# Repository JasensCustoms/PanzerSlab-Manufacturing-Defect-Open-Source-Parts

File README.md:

# Panzer SLAB — Manufacturing Defect Compatible Parts

Compatible replacement parts for the Panzer SLAB manufacturing defect. This repository holds basic PCB outlines, cable pinouts, and related files. You are welcome to fix errors, add context, and contribute to the repo.

## What's in This Repo

- `Main PCB/` — main PCB design files
- `Plexi Overlay/` — plexi overlay cut file / art template (all SLABs)
- `AUX PCB Files/` — AUX PCB design and production files
- `USB C PCB Files/` — USB-C PCB design and production files
- `3D Printed Parts/` — 3D-printable parts (main PCB fix spacers and taller aux button)

## Community & Discussion

Questions, ideas, or just want to talk builds? Join the Jasen's Customs Discord: [discord.gg/UJmNMunTqa](https://discord.gg/UJmNMunTqa)

## License — Personal, Non-Commercial Use Only

Copyright © 2026 Jasen Hicks ([www.JasensCustoms.com](https://www.JasensCustoms.com)). All rights reserved.

These designs are provided **solely for personal, private, non-commercial use.** You may build units for yourself, modify the designs for your own projects, and share the unmodified files (with attribution and the license intact). You may **not** sell parts, kits, units, or derivatives, manufacture for profit, or use these files commercially in any way.

Full terms — including the **No Warranty** and **No Support** notices — are in [LICENSE.md](LICENSE.md). By downloading, copying, or using any file in this repository, you agree to them.

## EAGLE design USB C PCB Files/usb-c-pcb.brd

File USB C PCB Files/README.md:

# USB C PCB Files

Design and production files for the SLAB USB-C PCB.

## What's in This Folder

- `usb-c-pcb.brd` / `usb-c-pcb.sch` — Autodesk EagleCAD board and schematic files
- `usb-c-pcb_2025-09-19.zip` — production files

## License & Community

Part of the [Panzer SLAB — Manufacturing Defect Compatible Parts](../README.md) repository. Provided for **personal, non-commercial use only** — full terms in [LICENSE.md](../LICENSE.md). Questions? Join the Jasen's Customs Discord: [discord.gg/UJmNMunTqa](https://discord.gg/UJmNMunTqa)

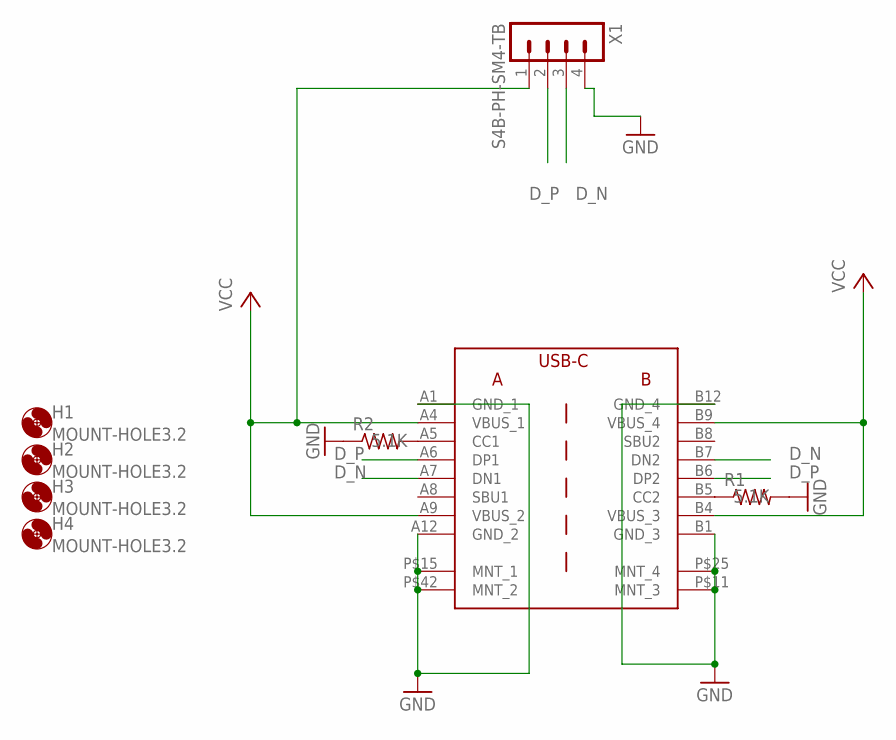
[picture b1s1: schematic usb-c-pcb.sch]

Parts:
H1, H2, H3, H4: MOUNT-HOLE3.2; 3,2
R1, R2: 5.1K; R0402
U$1: USB_TAYPE_C_16P
X1: S4B-PH-SM4-TB

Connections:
D_N: U$1.A7 (DN1), U$1.B7 (DN2), X1.3
D_P: U$1.A6 (DP1), U$1.B6 (DP2), X1.2
GND: R1.2, R2.1, U$1.A1 (GND_1), U$1.A12 (GND_2), U$1.B1 (GND_3), U$1.B12 (GND_4), U$1.P$11 (MNT_3), U$1.P$15 (MNT_1), U$1.P$25 (MNT_4), U$1.P$42 (MNT_2), X1.4
unnamed: R1.1, U$1.B5 (CC2)
unnamed: R2.2, U$1.A5 (CC1)
VCC: U$1.A4 (VBUS_1), U$1.A9 (VBUS_2), U$1.B4 (VBUS_3), U$1.B9 (VBUS_4), X1.1

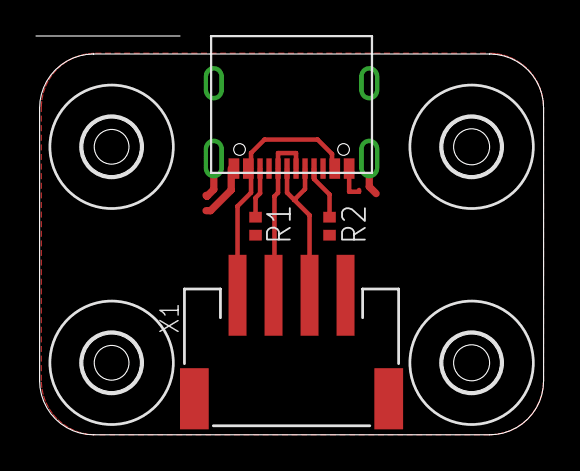
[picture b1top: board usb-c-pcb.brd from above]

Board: 2 copper layers, 28.2 x 22.2 mm, 8 parts (0 on the bottom side), 6 nets.

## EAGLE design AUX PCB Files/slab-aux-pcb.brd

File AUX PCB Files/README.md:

# AUX PCB Files

Design and production files for the SLAB AUX PCB.

## What's in This Folder

- `slab-aux-pcb.brd` / `slab-aux-pcb.sch` — Autodesk EagleCAD board and schematic files
- `slab-aux-pcb_2025-09-11.zip` — production files

## License & Community

Part of the [Panzer SLAB — Manufacturing Defect Compatible Parts](../README.md) repository. Provided for **personal, non-commercial use only** — full terms in [LICENSE.md](../LICENSE.md). Questions? Join the Jasen's Customs Discord: [discord.gg/UJmNMunTqa](https://discord.gg/UJmNMunTqa)

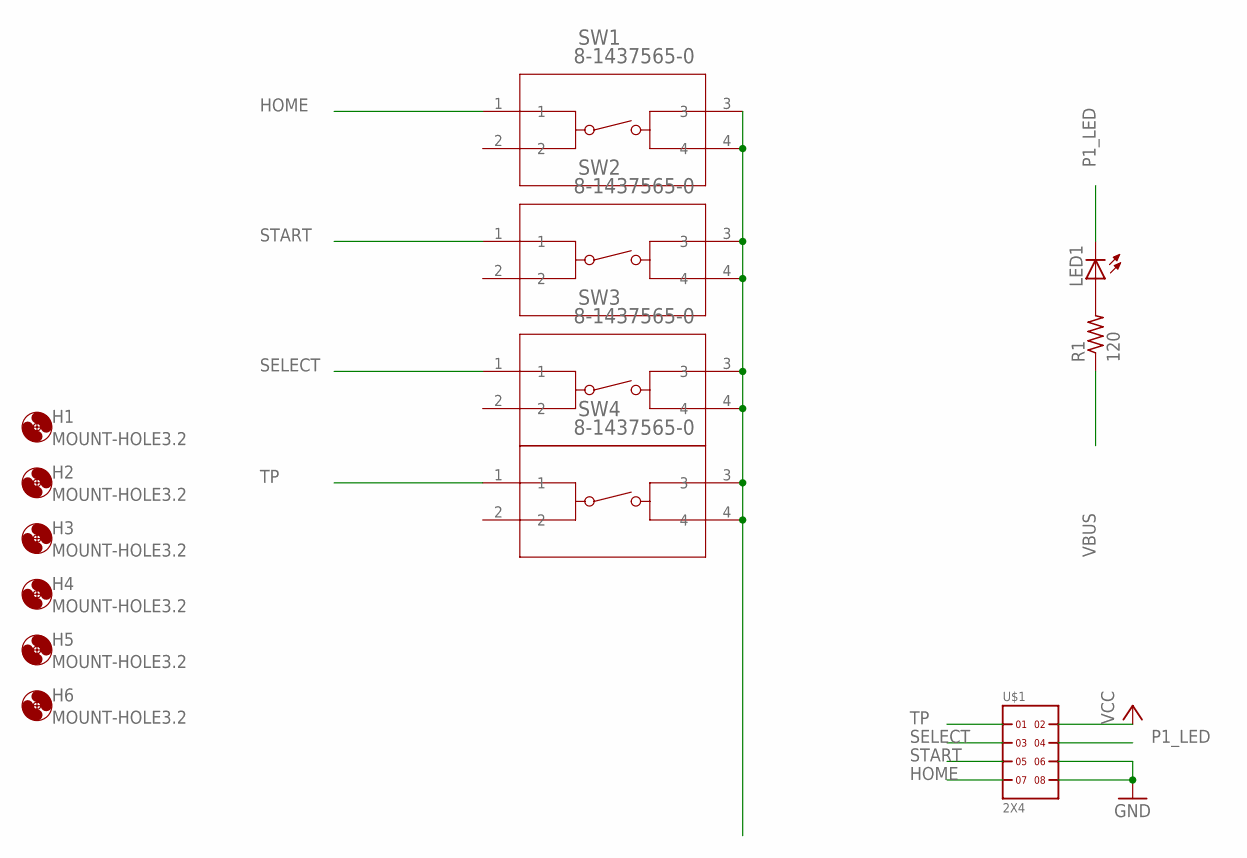
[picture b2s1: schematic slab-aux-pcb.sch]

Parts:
H1, H2, H3, H4, H5, H6: MOUNT-HOLE3.2; 3,2
LED1: LEDCHIP-LED0603; CHIP-LED0603
R1: 120; R0603
SW1, SW2, SW3, SW4: 8-1437565-0; SW4_1437565
U$1: 2X4

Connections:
GND: SW1.3, SW1.4, SW2.3, SW2.4, SW3.3, SW3.4, SW4.3, SW4.4, U$1.6, U$1.8
HOME: SW1.1, U$1.7
unnamed: LED1.A, R1.2
P1_LED: LED1.C, U$1.4
SELECT: SW3.1, U$1.3
START: SW2.1, U$1.5
TP: SW4.1, U$1.1
VBUS: R1.1, U$1.2

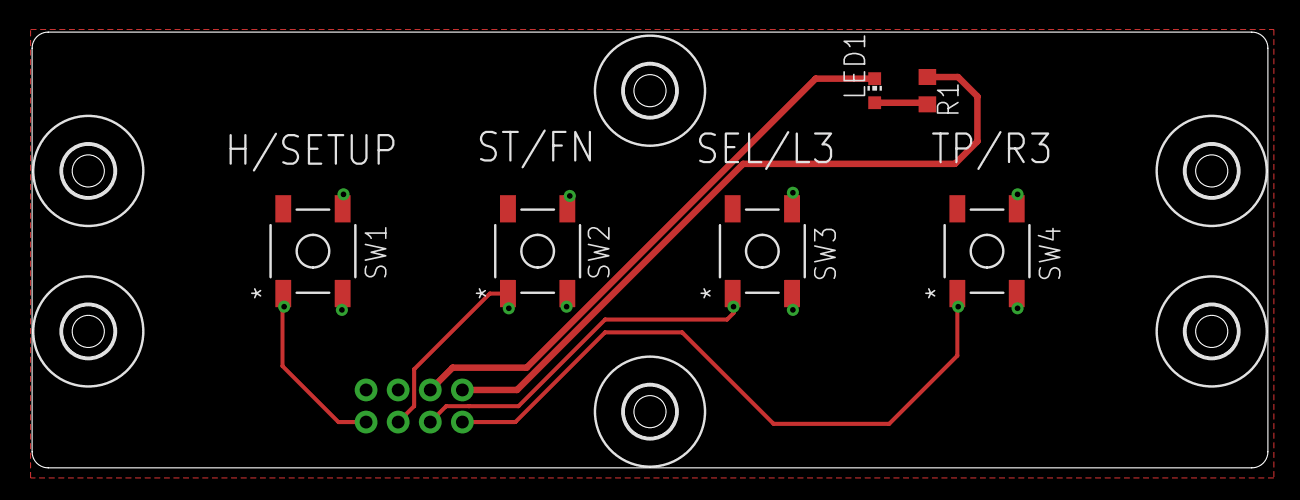
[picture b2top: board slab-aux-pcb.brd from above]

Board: 2 copper layers, 77.0 x 27.2 mm, 13 parts (1 on the bottom side), 8 nets.

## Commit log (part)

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2026-06-25 Update README with detailed license information
    Expanded description of the license terms and usage rights for the project.

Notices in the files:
parts and their libraries:
COPYRIGHT: Copyright (C) 2016 Accelerated Designs. All rights reserved
